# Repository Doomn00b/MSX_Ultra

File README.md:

# MSX_Ultra
 MSX2+ compatible Mini-ITX computer system, inspired by Sergey Kiselev's Omega Home Computer.

 This project is an open source implementation, and extension, of an MSX2+ compatible computer. The project is modular, and is built using a combination of 1980's-1990's era components - Z380 CPU, V9958 VDP, YM2610 PSG/FM-generator, and some newer components, such as 512 KiB SRAM and 512 KiB Flash ROM and dual FPGA's for the MSX-engine/Chipset (AT40K FPGAs).

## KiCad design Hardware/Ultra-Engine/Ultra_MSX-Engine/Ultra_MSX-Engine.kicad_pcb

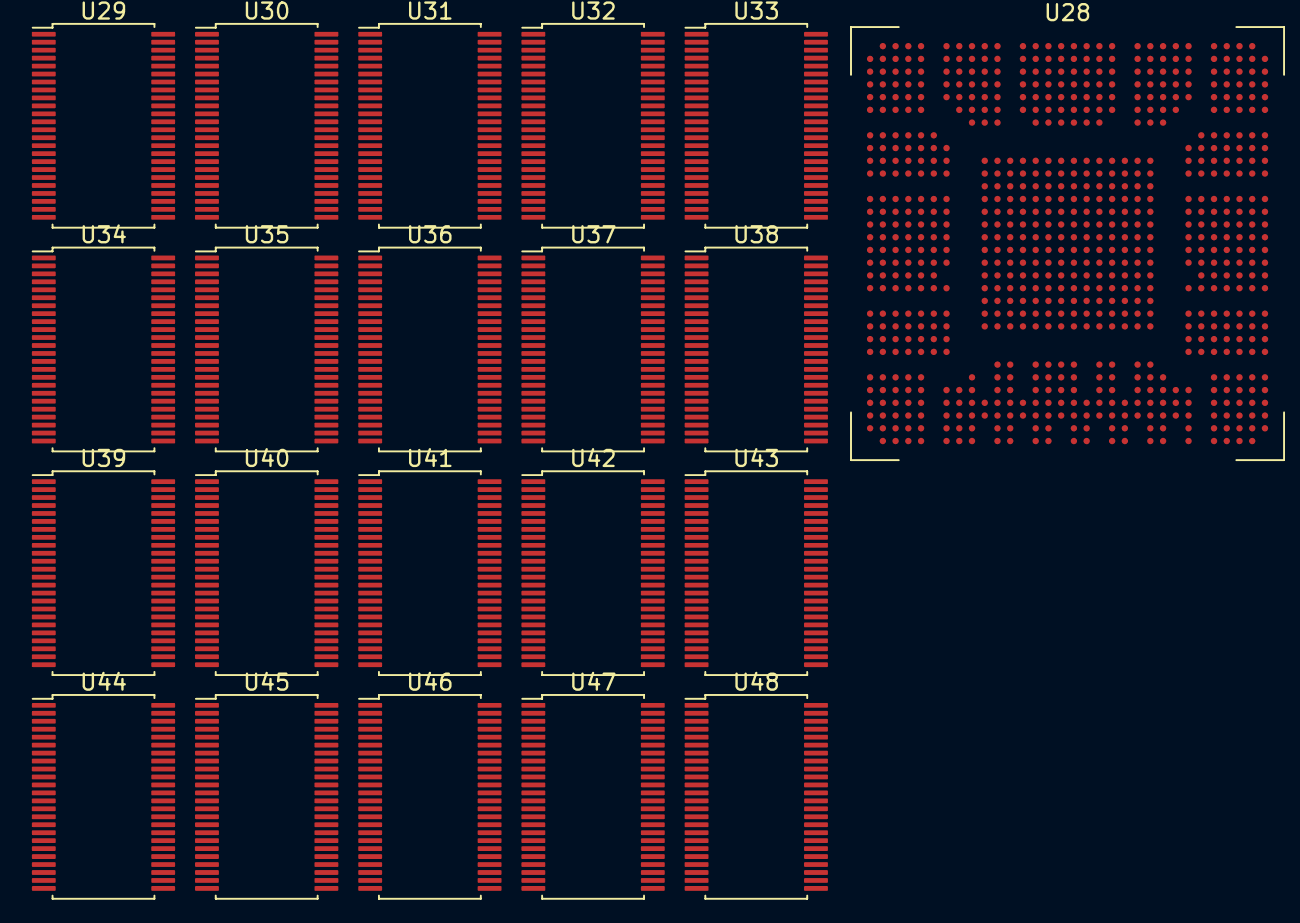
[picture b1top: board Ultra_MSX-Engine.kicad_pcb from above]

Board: 2 copper layers, 21 parts (0 on the bottom side), 35 nets, no tracks yet.

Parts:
U28: LFE5UM5G-85F-8BG756x; Lattice_caBGA-756_27.0x27.0mm_Layout27.8x27.8_P0.8mm
U29, U30, U31, U32, U33, U34, U35, U36, U37, U38, U39, U40, U41, U42, U43, U44, U45, U46, U47, U48: SN74LVCH16T245DGGR; TI_SN74LVCH16T245_6.2x12.6mm_P0.5mm

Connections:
unnamed: U28.AA11 (GND), U28.AA22 (GND), U28.AB11 (GND), U28.AB12 (GND), U28.AB13 (GND), U28.AB14 (GND), U28.AB15 (GND), U28.AB16 (GND), U28.AB17 (GND), U28.AB18 (GND), U28.AB19 (GND), U28.AB20 (GND), U28.AB21 (GND), U28.AB22 (GND), U28.AC12 (GND), U28.AC21 (GND), U28.AD2 (GND), U28.AD5 (GND), U28.AD28 (GND), U28.AD31 (GND), U28.AF11 (GND), U28.AF12 (GND), U28.AF14 (GND), U28.AF15 (GND), U28.AF16 (GND), U28.AF17 (GND), U28.AF19 (GND), U28.AF20 (GND), U28.AF23 (GND), U28.AG11 (GND), U28.AG14 (GND), U28.AG15 (GND), U28.AG16 (GND), U28.AG17 (GND), U28.AG20 (GND), U28.AG23 (GND), U28.AH2 (GND), U28.AH5 (GND), U28.AH7 (GND), U28.AH8 (GND), U28.AH11 (GND), U28.AH14 (GND), U28.AH15 (GND), U28.AH16 (GND), U28.AH17 (GND), U28.AH20 (GND), U28.AH23 (GND), U28.AH24 (GND), U28.AH25 (GND), U28.AH26 (GND), U28.AH29 (GND), U28.AH31 (GND), U28.AJ7 (GND), U28.AJ8 (GND), U28.AJ11 (GND), U28.AJ14 (GND), U28.AJ17 (GND), U28.AJ20 (GND), U28.AJ23 (GND), U28.AJ26 (GND), U28.AK7 (GND), U28.AK8 (GND), U28.AK11 (GND), U28.AK14 (GND), U28.AK17 (GND), U28.AK20 (GND), U28.AK23 (GND), U28.AK26 (GND), U28.AL2 (GND), U28.AL5 (GND), U28.AL7 (GND), U28.AL8 (GND), U28.AL9 (GND), U28.AL11 (GND), U28.AL12 (GND), U28.AL14 (GND), U28.AL15 (GND), U28.AL17 (GND), U28.AL18 (GND), U28.AL20 (GND), U28.AL21 (GND), U28.AL23 (GND), U28.AL24 (GND), U28.AL26 (GND), U28.AL29 (GND), U28.AL31 (GND), U28.AM7 (GND), U28.AM26 (GND), U28.B2 (GND), U28.B5 (GND), U28.B9 (GND), U28.B13 (GND), U28.B15 (GND), U28.B18 (GND), U28.B20 (GND), U28.B24 (GND), U28.B28 (GND), U28.B31 (GND), U28.E2 (GND), U28.E5 (GND), U28.E9 (GND), U28.E13 (GND), U28.E15 (GND), U28.E18 (GND), U28.E20 (GND), U28.E24 (GND), U28.E28 (GND), U28.E31 (GND), U28.J2 (GND), U28.J5 (GND), U28.J28 (GND), U28.J31 (GND), U28.K10 (GND), U28.K11 (GND), U28.K22 (GND), U28.K23 (GND), U28.L10 (GND), U28.L11 (GND), U28.L12 (GND), U28.L13 (GND), U28.L14 (GND), U28.L15 (GND), U28.L16 (GND), U28.L17 (GND), U28.L18 (GND), U28.L19 (GND), U28.L20 (GND), U28.L21 (GND), U28.L22 (GND), U28.L23 (GND), U28.M11 (GND), U28.M22 (GND), U28.N2 (GND), U28.N5 (GND), U28.N11 (GND), U28.N13 (GND), U28.N14 (GND), U28.N15 (GND), U28.N16 (GND), U28.N17 (GND), U28.N18 (GND), U28.N19 (GND), U28.N20 (GND), U28.N22 (GND), U28.N28 (GND), U28.N31 (GND), U28.P11 (GND), U28.P13 (GND), U28.P14 (GND), U28.P15 (GND), U28.P16 (GND), U28.P17 (GND), U28.P18 (GND), U28.P19 (GND), U28.P20 (GND), U28.P22 (GND), U28.R2 (GND), U28.R5 (GND), U28.R11 (GND), U28.R13 (GND), U28.R14 (GND), U28.R15 (GND), U28.R16 (GND), U28.R17 (GND), U28.R18 (GND), U28.R19 (GND), U28.R20 (GND), U28.R22 (GND), U28.R28 (GND), U28.R31 (GND), U28.T11 (GND), U28.T13 (GND), U28.T14 (GND), U28.T15 (GND), U28.T16 (GND), U28.T17 (GND), U28.T18 (GND), U28.T19 (GND), U28.T20 (GND), U28.T22 (GND), U28.U11 (GND), U28.U13 (GND), U28.U14 (GND), U28.U15 (GND), U28.U16 (GND), U28.U17 (GND), U28.U18 (GND), U28.U19 (GND), U28.U20 (GND), U28.U22 (GND), U28.V2 (GND), U28.V5 (GND), U28.V11 (GND), U28.V13 (GND), U28.V14 (GND), U28.V15 (GND), U28.V16 (GND), U28.V17 (GND), U28.V18 (GND), U28.V19 (GND), U28.V20 (GND), U28.V22 (GND), U28.V28 (GND), U28.V31 (GND), U28.W11 (GND), U28.W13 (GND), U28.W14 (GND), U28.W15 (GND)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
unnamed: U28.AA12 (VCC), U28.AA13 (VCC), U28.AA14 (VCC), U28.AA15 (VCC), U28.AA16 (VCC), U28.AA17 (VCC), U28.AA18 (VCC), U28.AA19 (VCC), U28.AA20 (VCC), U28.AA21 (VCC), U28.M12 (VCC), U28.M13 (VCC), U28.M14 (VCC), U28.M15 (VCC), U28.M16 (VCC), U28.M17 (VCC), U28.M18 (VCC), U28.M19 (VCC), U28.M20 (VCC), U28.M21 (VCC), U28.N12 (VCC), U28.N21 (VCC), U28.P12 (VCC), U28.P21 (VCC), U28.R12 (VCC), U28.R21 (VCC), U28.T12 (VCC), U28.T21 (VCC), U28.U12 (VCC), U28.U21 (VCC), U28.V12 (VCC), U28.V21 (VCC), U28.W12 (VCC), U28.W21 (VCC), U28.Y12 (VCC), U28.Y21 (VCC)
unnamed: U28.AG9 (VCCA0), U28.AG12 (VCCA0), U28.AH9 (VCCA0), U28.AH12 (VCCA0), U28.AJ9 (VCCA0), U28.AJ10 (VCCA0), U28.AJ12 (VCCA0), U28.AJ13 (VCCA0)
unnamed: U28.AF22 (VCCA1), U28.AG19 (VCCA1), U28.AG22 (VCCA1), U28.AH19 (VCCA1), U28.AH22 (VCCA1), U28.AJ18 (VCCA1), U28.AJ19 (VCCA1), U28.AJ21 (VCCA1), U28.AJ22 (VCCA1)
unnamed: U28.AC11 (VCCAUX), U28.AC22 (VCCAUX), U28.K13 (VCCAUX), U28.K20 (VCCAUX), U28.N10 (VCCAUX), U28.N23 (VCCAUX), U28.Y10 (VCCAUX), U28.Y23 (VCCAUX)
unnamed: U28.AJ15 (VCCAUXA0), U28.AJ16 (VCCAUXA0)
unnamed: U28.AJ24 (VCCAUXA1), U28.AJ25 (VCCAUXA1)
unnamed: U28.K12 (VCCIO0), U28.K14 (VCCIO0), U28.K15 (VCCIO0), U28.K16 (VCCIO0)
unnamed: U28.K17 (VCCIO1), U28.K18 (VCCIO1), U28.K19 (VCCIO1), U28.K21 (VCCIO1)
unnamed: U28.M23 (VCCIO2), U28.P23 (VCCIO2), U28.R23 (VCCIO2), U28.T23 (VCCIO2)
unnamed: U28.AA23 (VCCIO3), U28.U23 (VCCIO3), U28.V23 (VCCIO3), U28.W23 (VCCIO3)
unnamed: U28.AB23 (VCCIO4), U28.AC23 (VCCIO4)
unnamed: U28.AA10 (VCCIO6), U28.U10 (VCCIO6), U28.V10 (VCCIO6), U28.W10 (VCCIO6)
unnamed: U28.M10 (VCCIO7), U28.P10 (VCCIO7), U28.R10 (VCCIO7), U28.T10 (VCCIO7)
unnamed: U28.AB10 (VCCIO8), U28.AC10 (VCCIO8)
unnamed: U29.4 (GND), U29.10 (GND_2), U29.15 (GND_3), U29.21 (GND_4), U29.28 (GND_5), U29.34 (GND_6), U29.39 (GND_7), U29.45 (GND_8)
unnamed: U30.4 (GND), U30.10 (GND_2), U30.15 (GND_3), U30.21 (GND_4), U30.28 (GND_5), U30.34 (GND_6), U30.39 (GND_7), U30.45 (GND_8)
unnamed: U31.4 (GND), U31.10 (GND_2), U31.15 (GND_3), U31.21 (GND_4), U31.28 (GND_5), U31.34 (GND_6), U31.39 (GND_7), U31.45 (GND_8)
unnamed: U32.4 (GND), U32.10 (GND_2), U32.15 (GND_3), U32.21 (GND_4), U32.28 (GND_5), U32.34 (GND_6), U32.39 (GND_7), U32.45 (GND_8)
unnamed: U33.4 (GND), U33.10 (GND_2), U33.15 (GND_3), U33.21 (GND_4), U33.28 (GND_5), U33.34 (GND_6), U33.39 (GND_7), U33.45 (GND_8)
unnamed: U34.4 (GND), U34.10 (GND_2), U34.15 (GND_3), U34.21 (GND_4), U34.28 (GND_5), U34.34 (GND_6), U34.39 (GND_7), U34.45 (GND_8)
unnamed: U35.4 (GND), U35.10 (GND_2), U35.15 (GND_3), U35.21 (GND_4), U35.28 (GND_5), U35.34 (GND_6), U35.39 (GND_7), U35.45 (GND_8)
unnamed: U36.4 (GND), U36.10 (GND_2), U36.15 (GND_3), U36.21 (GND_4), U36.28 (GND_5), U36.34 (GND_6), U36.39 (GND_7), U36.45 (GND_8)
unnamed: U37.4 (GND), U37.10 (GND_2), U37.15 (GND_3), U37.21 (GND_4), U37.28 (GND_5), U37.34 (GND_6), U37.39 (GND_7), U37.45 (GND_8)
unnamed: U38.4 (GND), U38.10 (GND_2), U38.15 (GND_3), U38.21 (GND_4), U38.28 (GND_5), U38.34 (GND_6), U38.39 (GND_7), U38.45 (GND_8)
unnamed: U39.4 (GND), U39.10 (GND_2), U39.15 (GND_3), U39.21 (GND_4), U39.28 (GND_5), U39.34 (GND_6), U39.39 (GND_7), U39.45 (GND_8)
unnamed: U40.4 (GND), U40.10 (GND_2), U40.15 (GND_3), U40.21 (GND_4), U40.28 (GND_5), U40.34 (GND_6), U40.39 (GND_7), U40.45 (GND_8)
unnamed: U41.4 (GND), U41.10 (GND_2), U41.15 (GND_3), U41.21 (GND_4), U41.28 (GND_5), U41.34 (GND_6), U41.39 (GND_7), U41.45 (GND_8)
unnamed: U42.4 (GND), U42.10 (GND_2), U42.15 (GND_3), U42.21 (GND_4), U42.28 (GND_5), U42.34 (GND_6), U42.39 (GND_7), U42.45 (GND_8)
unnamed: U43.4 (GND), U43.10 (GND_2), U43.15 (GND_3), U43.21 (GND_4), U43.28 (GND_5), U43.34 (GND_6), U43.39 (GND_7), U43.45 (GND_8)
unnamed: U44.4 (GND), U44.10 (GND_2), U44.15 (GND_3), U44.21 (GND_4), U44.28 (GND_5), U44.34 (GND_6), U44.39 (GND_7), U44.45 (GND_8)
unnamed: U45.4 (GND), U45.10 (GND_2), U45.15 (GND_3), U45.21 (GND_4), U45.28 (GND_5), U45.34 (GND_6), U45.39 (GND_7), U45.45 (GND_8)
unnamed: U46.4 (GND), U46.10 (GND_2), U46.15 (GND_3), U46.21 (GND_4), U46.28 (GND_5), U46.34 (GND_6), U46.39 (GND_7), U46.45 (GND_8)
unnamed: U47.4 (GND), U47.10 (GND_2), U47.15 (GND_3), U47.21 (GND_4), U47.28 (GND_5), U47.34 (GND_6), U47.39 (GND_7), U47.45 (GND_8)
unnamed: U48.4 (GND), U48.10 (GND_2), U48.15 (GND_3), U48.21 (GND_4), U48.28 (GND_5), U48.34 (GND_6), U48.39 (GND_7), U48.45 (GND_8)

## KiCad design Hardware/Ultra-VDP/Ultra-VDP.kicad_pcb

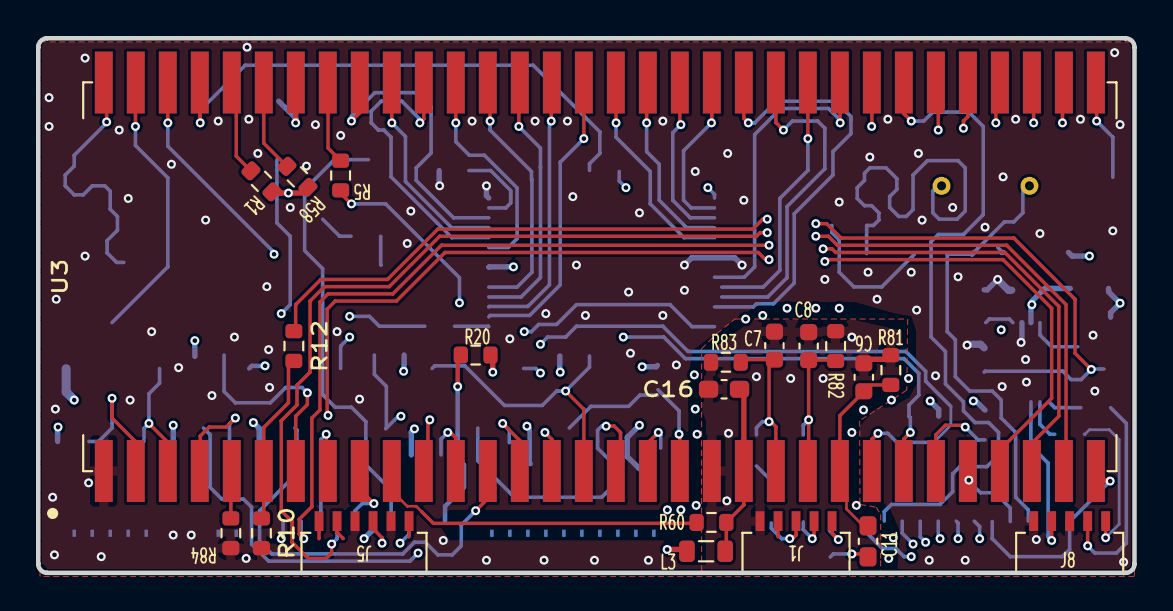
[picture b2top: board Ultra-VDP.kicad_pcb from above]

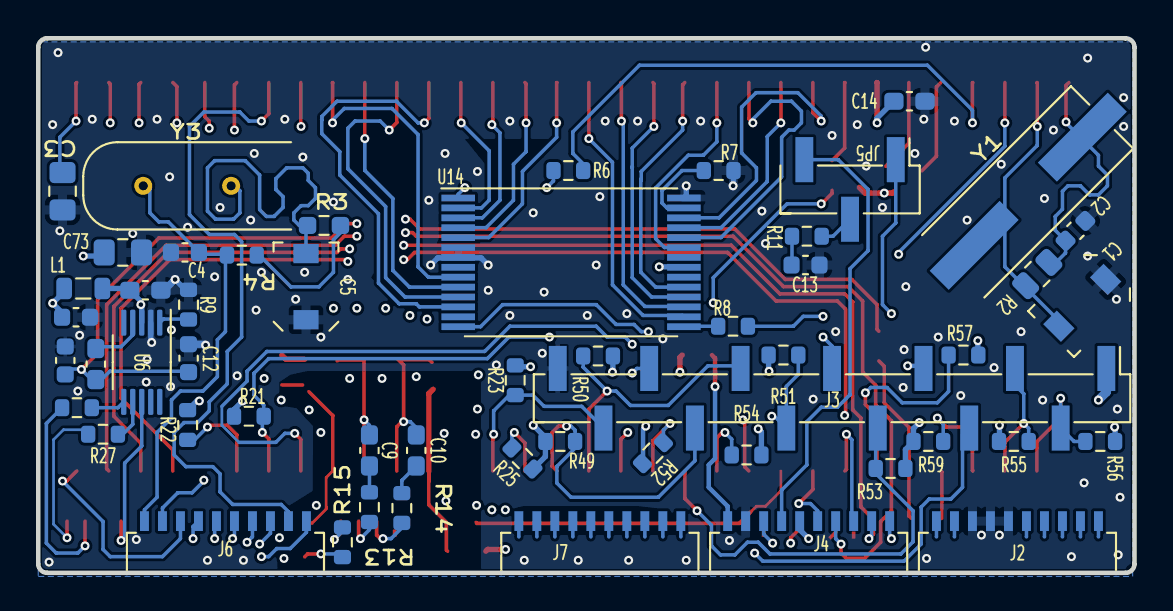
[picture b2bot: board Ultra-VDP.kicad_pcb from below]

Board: 4 copper layers, 60.9 x 29.7 mm, 95 parts (70 on the bottom side), 110 nets.

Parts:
C1, C5: CTRIM_SGC3S300NM; C_Trimmer_Sprague-Goodman_SGC3
C2, C4: 22pF; C_0603_1608Metric
C3: C_CL21B223KBANFNC; C_0805_2012Metric_Pad1.18x1.45mm_HandSolder
C6, C7, C8: 330pF; C_0603_1608Metric
C9, C10, C11, C14, C15, C16, C17: C_CL10B104KB8NNNL; C_0603_1608Metric_Pad1.08x0.95mm_HandSolder
C12, C19: C_CC0603JRNPO9BN470; C_0603_1608Metric
C13: 4.7pF; C_0603_1608Metric
C18: C_GRM188D71A106KA73D; C_0603_1608Metric
C73: C_GRM21BR71A106KA73K; C_0805_2012Metric_Pad1.18x1.45mm_HandSolder
J1, J8: BC075-05; GCT_BC075-05_PinHeader_1x05_P1.00mm_Horizontal_SMD
J2, J4, J6, J7: BC075-10; GCT_BC075-10_PinHeader_1x10_P1.00mm_Horizontal_SMD
J3: CBUS; PinHeader_1x13_P2.54mm_Vertical_SMD_Pin1Left_lrj
J5: BC075-06; GCT_BC075-06_PinHeader_1x06_P1.00mm_Horizontal_SMD
JP5: NTSC/PAL; PinHeader_1x03_P2.54mm_Vertical_SMD_Pin1Left_sc
L1, L3: L_MLZ2012M4R7HT000; L_0805_2012Metric
R1, R7, R9, R20, R21, R22, R23, R25, R49, R50, R51, R52, R53, R54, R55, R56, R57, R58, R59, R60: R_RC0603FR-0710KL; R_0603_1608Metric_roundcourt
R2: 470k; R_0805_2012Metric
R3: R_ERA-3VRW1001V; R_0603_1608Metric_Pad0.98x0.95mm_HandSolder
R4: R_ERJ-3GEYJ105V; R_0603_1608Metric
R5, R6, R8, R12, R27, R61: R_CRGP0603F220R; R_0603_1608Metric
R10, R13, R14, R15: R_ERJ-PA3F75R0V; R_0603_1608Metric_roundcourt
R11: 2.2k; R_0603_1608Metric
R81, R82, R83, R84: R_CRG0603F470R; R_0603_1608Metric
U3: V9958; DIP-64_W19.05mm_SMDSocket_SmallPads
U6: LMH1980; VSSOP-10_3x3mm_P0.5mm
U14: V53C8125HT30; TSOP-I-28_11.8x8mm_P0.55mm
Y1: Y_HCM4921477270ABJT; Crystal_HC49-US_Vertical_SMD
Y3: Y_ECS-44-20-4X; Crystal_HC49-US_Vertical_THT
trace1, trace2, trace3, trace4, trace6, trace7, trace8, trace9, trace10, trace11, trace12, trace13, trace14, trace15, trace16, trace17, trace18, trace19, trace20, trace21, trace22: pcb-trace; NetTie-2_SMD_Pad0.2mm

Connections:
+5V: C14.2, C18.1, C73.1, J3.1, J4.5, L1.1, L3.1, R1.1, R20.1, R21.2, R22.2, R23.2, R25.2, R49.2, R50.2, R51.2, R52.2, R53.2, R54.2, R55.2, R56.2, R57.2, R58.2, R59.2, U3.58 (VDD), U14.21 (VCC)
/A0: J5.4, U3.29 (MODE0)
/A1: J6.2, U3.28 (MODE1)
/A2: J7.4, trace9.1
/A3: J7.5, trace10.1
/A4: J7.6, trace11.1
/A5: J7.7, trace12.1
/A6: J7.8, trace13.1
/A7: J7.9, trace14.1
/A8: J7.10, trace15.1
/B-Mb: J1.5, R15.2
/BLANK: J5.6, trace4.1
/BLEO: R57.1, U3.7 (BLEO)
/BLUE1: C6.1, C11.2, R81.1, U3.24 (B)
/BLUE2: C11.1, R15.1
/CB0: J3.12, R23.1, U3.19 (C0)
/CB1: J3.11, R25.1, U3.18 (C1)
/CB2: J3.10, R49.1, U3.17 (C2)
/CB3: J3.9, R50.1, U3.16 (C3)
/CB4: J3.8, R51.1, U3.15 (C4)
/CB5: J3.7, R52.1, U3.14 (C5)
/CB6: J3.6, R53.1, U3.13 (C6)
/CB7: J3.5, R54.1, U3.12 (C7)
/CBDR: J3.4, U3.11 (CBDR)
/CLK_VDP: J4.8, U3.8 (~VDS/CPUCLK)
/COMPSYNC: R10.2, R12.2, U3.6 (CSYNC)
/CSYNC: J8.2, U6.8 (CSOUT)
/D0: J6.10, U3.40 (CD0)
/D1: J6.9, U3.39 (CD1)
/D2: J6.8, U3.38 (CD2)
/D3: J6.7, U3.37 (CD3)
/D4: J6.6, U3.36 (CD4)
/D5: J6.5, U3.35 (CD5)
/D6: J6.4, U3.34 (CD6)
/D7: J6.3, U3.32 (CD7)
/D8: J2.2, trace17.1
/D9: J2.1, trace16.1
/D10: J5.1, trace2.1
/D11: J5.2, trace3.1
/D12: J2.6, trace18.1
/D13: J7.1, trace6.1
/D14: J7.2, trace7.1
/D15: J7.3, trace8.1
/G-Mb: J1.3, R14.2
/GREEN1: C7.1, C10.2, R83.1, U3.22 (G)
/GREEN2: C10.1, R14.1
/HORSYNC: R84.1, U3.5 (HSYNC)
/HSYNC: J8.4, R61.1
/NTSC_CLKO: J4.10, JP5.1
/PAL_CLK_IN+: C4.2, J6.1, R4.1, Y3.1
/PAL_CLK_IN-: C5.2, R3.2, Y3.2
/PAL_CLK_OUT: J4.4, JP5.3
/R-Mb: J1.4, R13.2
/RED1: C8.1, C9.2, R82.1, U3.23 (R)
/RED2: C9.1, R13.1
/SYNCIN: C15.1, U6.4 (VIN)
/TCK: J2.9, trace21.1
/TDI: J2.8, trace20.1
/TDO: J2.10, trace22.1
/TMS: J2.7, trace19.1
/VA0: U3.49 (AD0), U14.16 (A0)
/VA1: U3.50 (AD1), U14.17 (A1)
/VA2: U3.51 (AD2), U14.18 (A2)
/VA3: U3.52 (AD3), U14.19 (A3)
/VA4: U3.53 (AD4), U14.23 (A4)
/VA5: U3.54 (AD5), U14.24 (A5)
/VA6: U3.55 (AD6), U14.25 (A6)
/VA7: U3.56 (AD7), U14.26 (A7)
/VD0: U3.41 (RD0), U14.9 (IO1)
/VD1: U3.42 (RD1), U14.10 (IO2)
/VD2: U3.43 (RD2), U14.11 (IO3)
/VD3: U3.44 (RD3), U14.12 (IO4)
/VD4: U3.45 (RD4), U14.2 (IO5)
/VD5: U3.46 (RD5), U14.3 (IO6)
/VD6: U3.47 (RD6), U14.4 (IO7)
/VD7: U3.48 (RD7), U14.5 (IO8)
/VREF: J1.2, trace1.1
/VSYNC: J8.5, R27.1
/V_CLK: C13.1, R11.1
/XTAL1+: C1.2, R2.2, U3.63 (XTAL1/CLKIN), Y1.2
/XTAL-: C2.2, R2.1, U3.64 (XTAL2), Y1.1
/~CAS0: R6.1, U14.1 (~CAS)
/~CAS1: R1.2, U3.60 (~CAS1)
/~CASX: R58.1, U3.59 (~CASX)
/~DHCLK: J3.2, R56.1, U3.2 (~DHCLK)
/~DLCLK: J3.3, R55.1, U3.3 (~DLCKL)
/~HRESET: R22.1, U3.27 (~HRESET)
/~RAS_: R8.2, U3.62 (~RAS)
/~RAS: R8.1, U14.15 (~RAS)
/~RESET: J4.6, U3.9 (~RESET)
/~VDP_INT: J4.1, R20.2, U3.25 (~INT)
/~VDP_RD: J4.7, U3.31 (~CSR)
/~VDP_WAIT: J4.3, R21.1, U3.26 (~WAIT)
/~VDP_WR: J4.9, U3.30 (~CSW)
/~VRESET: R59.1, U3.4 (~VRESET)
/~VWR: R5.1, U14.14 (~WE)
/~YS: R60.1, U3.10 (~YS)
GND: C1.1, C2.1, C3.2, C4.1, C5.1, C6.2, C7.2, C8.2, C12.2, C13.2, C14.1, C16.1, C17.2, C18.2, C19.2, C73.2, J1.1, J2.3, J2.4, J2.5, J3.13, J4.2, J5.3, J5.5, J8.1, J8.3, R7.1, R9.1, R10.1, R81.2, R82.2, R83.2, R84.2, U3.1 (GND), U3.20 (GNDA), U6.2 (GND), U14.6 (VSS), U14.7 (VSS), U14.28 (~OE)
unnamed: C12.1, C15.2, C19.1, R12.1
unnamed: JP5.2, R11.2
unnamed: R3.1, R4.2
unnamed: R5.2, U3.57 (R/~W)
unnamed: R6.2, U3.61 (~CAS0)
unnamed: C3.1, U3.33 (VBB)
unnamed: R61.2, U6.6 (HSOUT)
unnamed: R9.2, U6.1 (REXT)
unnamed: R27.2, U6.7 (VSOUT)
unnamed: R7.2, U14.27 (A8)
VCCVDP: C16.2, L3.2, R60.2, U3.21 (VDDA)
VDDSYNC: C17.1, L1.2, U6.3 (VCC)

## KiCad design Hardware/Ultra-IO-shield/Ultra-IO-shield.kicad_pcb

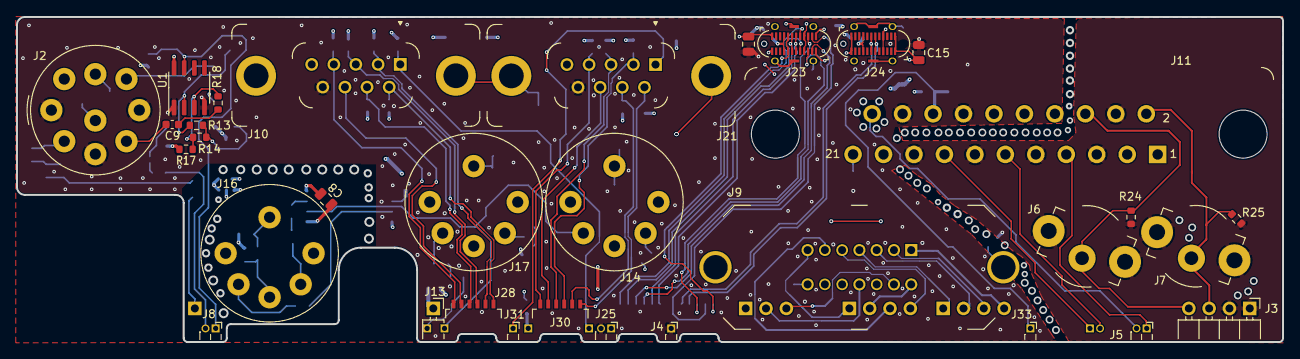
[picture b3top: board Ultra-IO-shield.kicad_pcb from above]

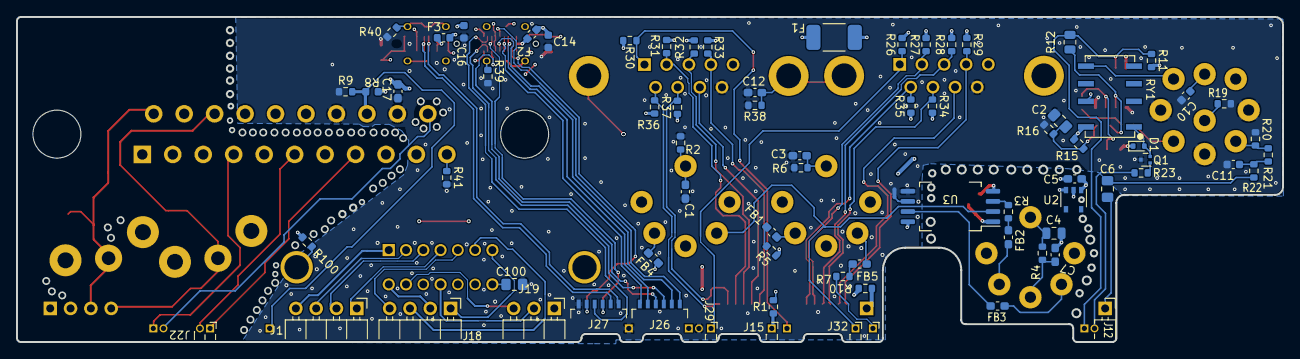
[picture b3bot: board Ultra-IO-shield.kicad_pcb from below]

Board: 4 copper layers, 158.3 x 40.6 mm, 108 parts (75 on the bottom side), 93 nets.

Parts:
C1, C3, C5, C7, C12, C17: C_CL10B104KB8NNNL; C_0603_1608Metric_Pad1.08x0.95mm_HandSolder
C2: C_GRM21BR71A106KA73K; C_0805_2012Metric_Pad1.18x1.45mm_HandSolder
C4, C8: C_CL21B103KBANNNC; C_0805_2012Metric
C6, C100: C_CL21B105KBFNNNF; C_0805_2012Metric_Pad1.18x1.45mm_HandSolder
C9, C11: 22nF; C_0603_1608Metric
C10: 0.1uF; C_0603_1608Metric
C13, C15: C_GRM21BR61A476ME15K; C_0805_2012Metric
C14, C16: C_CL10B104KB8NNNL; C_0603_1608Metric_round_court
D1: 1N4148WT; D_SOD-523
F1: PPTC_SMD1812B075TF; Yageo_Fuse_1812_4532Metric
F2, F3: PPTC_0603L075; Fuse_0603_1608Metric
FB1, FB2, FB3, FB4, FB5: L_ferrite_BLM18KG102SZ1D; L_0603_1608Metric_Pad1.05x0.95mm_HandSolder
J1, J3, J18: Conn_01x04; PinHeader_1x04_P2.54mm_Horizontal_less-silk
J2: DIN-8_SD-80BV; Jack_DIN_CUI_SD-80BV_Vertical
J4, J15, J20, J29, J31, J32, J33: Conn_01x02; PinHeader_1x01_P1.27mm_Horizontal_less-silk
J5, J8, J22, J25: Conn_01x02; PinHeader_1x02_P1.27mm_Horizontal_less-silk
J6: Conn_RCJ-023; CUI_RCJ-023
J7: Conn_RCJ-022; CUI_RCJ-022
J9: NorComp_111-014-213L001; Conn_Micro_Ribbon_14F_Vertical
J10, J21: ASSMANN_A-DF_09_PP/Z; Assmann_A-DF09PP_Z_Female_Vertical_P2.77x2.84mm
J11: TC_1578891_SCART; SCART-21_Female_Vertical_P1.905x2.54mm_EdgePinOffset10.7mm
J12, J13: Conn_01x01; PinHeader_1x01_P2.54mm_Horizontal_less-silk
J14, J16, J17: CUI_SD-50BV; Jack_DIN_CUI_SD-50BV_Vertical
J19: Conn_01x03; PinHeader_1x03_P2.54mm_Horizontal_less-silk
J23, J24: USB_C_GCT_USB4115-03-C; GCT_USB4115-03-C_modified
J26, J27, J28, J30: BC075-06; GCT_BC075-06_PinHeader_1x06_P1.00mm_Horizontal_SMD_less-silk
Q1: MMBT2907AM3T5G; SOT-723
R1, R3, R5, R7: R_CRGP0603F220R; R_0603_1608Metric
R2, R4, R6, R19, R38, R39, R40, R41, R100: R_ERJ-3GEYJ105V; R_0603_1608Metric
R8: 100; C_0603_1608Metric_round_court
R9: 100; R_0603_1608Metric
R10: 1k; R_0603_1608Metric
R11, R23: 1K; R_0603_1608Metric
R12: 220K; R_0805_2012Metric_roundcourt
R13, R21, R22: 4.7K; R_0603_1608Metric
R14, R18: 10K; R_0603_1608Metric
R15, R16: 2.7K; R_0603_1608Metric
R17: 470K; R_0603_1608Metric
R20: 100R; R_0603_1608Metric
R24, R25: 47k; R_0603_1608Metric
R26, R27, R28, R29, R30, R31, R32, R33, R34, R35, R36, R37: R_RC0603FR-074K7L; R_0603_1608Metric
RY1: TE_IM43GR; Relay_DPDT_AXICOM_IMSeries_GullWing
TP1: NetTie-2_small_round; NetTie-2_SMD_Pad0.5mm
U1: LM211; SOIC-8_3.9x4.9mm_P1.27mm
U2: AP7370; DIODES_SOT-753_SC-74A
U3: ADuM226; TEXAS_RI-8-1_7.5x5.85mm_P1.27mm

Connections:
+5V: C14.1, C16.1, D1.1 (K), F1.1, F2.2, F3.2, J15.1, J19.1, J25.1, R1.1, R5.1, R8.1, R11.2, R15.2, R17.1, R26.2, R27.2, R28.2, R29.2, R30.2, R31.2, R32.2, R33.2, R34.2, R35.2, R36.2, R37.2, RY1.8, U1.8 (V+), U3.8 (VDD2)
+12V: C5.1, J13.1, R10.2, U2.1 (VIN)
/+5VD: C8.1, U2.3 (VOUT), U3.1 (VDD1)
/+5_joy: F1.2, J10.5, J21.5
/+12V-1K: C17.1, J11.8 (SW), R10.1
/AUD_L: J3.4, J6.2 (IN2), J11.6 (AIL/MONO), R24.1
/AUD_R: J3.3, J7.2 (IN2), J11.2 (AIR), R25.2
/BLANK: J11.16 (BLNK), J33.1, R8.2, R9.1
/BOUT: J5.1, J11.7 (BLUE)
/CAS_I: C9.1, J2.5
/CAS_IN: J8.1, R11.1, R12.2, U1.7 (COL_OUT)
/CAS_MOT: J8.2, R23.1
/CAS_O: J2.4, R20.1, R21.2
/CAS_OUT: C6.2, J12.1
/CC1/HPD: J23.A5 (CC1), J23.B5 (CC2), J27.2
/CSINKi: FB3.1, U3.7 (VIA)
/CSINKo: FB1.2, R5.2
/CSRCi: R3.1, U3.3 (VIB)
/CSRCo: FB5.1, R7.2
/CSYNC: J5.2, J11.20 (VIDIN/Sync)
/GND_U: C13.1, C15.1, J23.A1 (GND), J23.A12 (GND), J23.B1 (GND), J23.B12 (GND), J24.A1 (GND), J24.A12 (GND), J24.B1 (GND), J24.B12 (GND)
/GND/SBU2: J23.B8 (SBU2), J26.5
/GOUT: J11.11 (GREEN), J22.2
/JOY_OUT_A: J10.8, J28.2
/JOY_OUT_B: J21.8, J30.2
/MID_RX: J14.5, J32.1, U3.2 (VOA)
/MID_TX: J20.1, R7.1
/N_O: J2.7, RY1.5
/PD0: J1.3, J9.2
/PD1: J1.2, J9.3
/PD2: J1.1, J9.4
/PD3: J9.5, J18.4
/PD4: J9.6, J18.3
/PD5: J9.7, J18.1
/PD6: J9.8, J18.2
/PD7: J9.9, J19.3
/PRT_BUSY: J9.11, J19.2
/ROUT: J11.15 (RED/CHROMA), J22.1
/RY_5V: J2.6, RY1.7
/SH1: J23.SH (SHIELD), R39.2
/SH2: J24.SH (SHIELD), R40.2
/SH3: J11.21 (SH), R41.1
/SWDCLK/RX1-: J23.B10 (RX1-), J26.3
/SWDIO/RX1+: J23.B11 (RX1+), J26.4
/SWO/RX2-: J23.A10 (RX2-), J27.4
/USB1_D+: J23.A7 (D1-), J23.B7 (D2-), J26.1
/USB1_D-: J23.A6 (D1+), J23.B6 (D2+), J26.2
/USB2_D+: J24.A6 (D1+), J24.B6 (D2+), J27.6
/USB2_D-: J24.A7 (D1-), J24.B7 (D2-), J27.5
/VBUS1: F2.1, J23.A4 (VBUS), J23.A9 (VBUS), J23.B4 (VBUS), J23.B9 (VBUS)
/VBUS2: F3.1, J24.A4 (VBUS), J24.A9 (VBUS), J24.B4 (VBUS), J24.B9 (VBUS)
/VCT/SBU1: J23.A8 (SBU1), J26.6
/nRESET/RX2+: J23.A11 (RX2+), J27.3
/~BCK_A: J10.2, J28.5, R27.1
/~BCK_B: J21.2, J30.4, R31.1
/~FWD_A: J10.1, J29.1, R26.1
/~FWD_B: J21.1, J31.1, R30.1
/~LFT_A: J10.3, J28.4, R28.1
/~LFT_B: J21.3, J30.3, R32.1
/~RGT_A: J10.4, J28.1, R29.1
/~RGT_B: J21.4, J30.1, R33.1
/~STROBE: J1.4, J9.1
/~TRG1_A: J10.6, J28.6, R35.1
/~TRG1_B: J21.6, J30.6, R36.1
/~TRG2_A: J10.7, J28.3, R34.1
/~TRG2_B: J21.7, J30.5, R37.1
GND: C1.2, C2.2, C3.2, C10.2, C11.2, C12.2, C13.2, C14.2, C15.2, C16.2, C17.2, C100.2, J2.1, J2.2, J2.3, J3.1, J3.2, J4.1, J6.1A (IN1), J6.1B (IN1), J7.1A (IN1), J7.1B (IN1), J10.9, J11.4 (AUGND), J11.5 (BGND), J11.9 (GGND), J11.13 (RGND), J11.14 (DATGND), J11.17 (VGND), J11.18 (BLNKGND), J21.9, J25.2, J27.1, Q1.3 (C), R2.1, R6.1, R9.2, R16.2, R19.1, R20.2, R24.2, R25.1, R38.1, R39.1, R40.1, R41.2, R100.1, TP1.1, U1.1 (GND), U1.4 (V-), U3.5 (GND2)
GND2: C4.2, C5.2, C7.2, C8.2, U2.2 (GND), U3.4 (GND1)
unnamed: C1.1, J14.2, J14.G, R2.2
unnamed: C2.1, R13.1, R14.2, R15.1, R16.1
unnamed: C3.1, J17.2, J17.G, R6.2
unnamed: C4.1, J16.G, R4.2
unnamed: C6.1, R22.1
unnamed: C7.1, J16.2, R4.1
unnamed: C9.2, R18.2
unnamed: C10.1, J2.SH
unnamed: C11.1, R21.1, R22.2
unnamed: C12.1, J10.SH, J21.SH, R38.2
unnamed: D1.2 (A), Q1.2 (E), RY1.1
unnamed: FB1.1, J17.4
unnamed: FB2.1, J16.4
unnamed: FB2.2, R3.2
unnamed: FB3.2, J16.5
unnamed: FB4.1, J14.4
unnamed: FB4.2, R1.2
unnamed: FB5.2, J17.5
unnamed: J2.8, R19.2
unnamed: C100.1, J9.14
unnamed: J9.15 (SH), J9.16 (SH2), R100.2
unnamed: Q1.1 (B), R23.2
unnamed: R12.1, R13.2, U1.2 (+)
unnamed: R14.1, R17.2, R18.1, U1.3 (-)
unnamed: TP1.2, U3.6 (VOB)

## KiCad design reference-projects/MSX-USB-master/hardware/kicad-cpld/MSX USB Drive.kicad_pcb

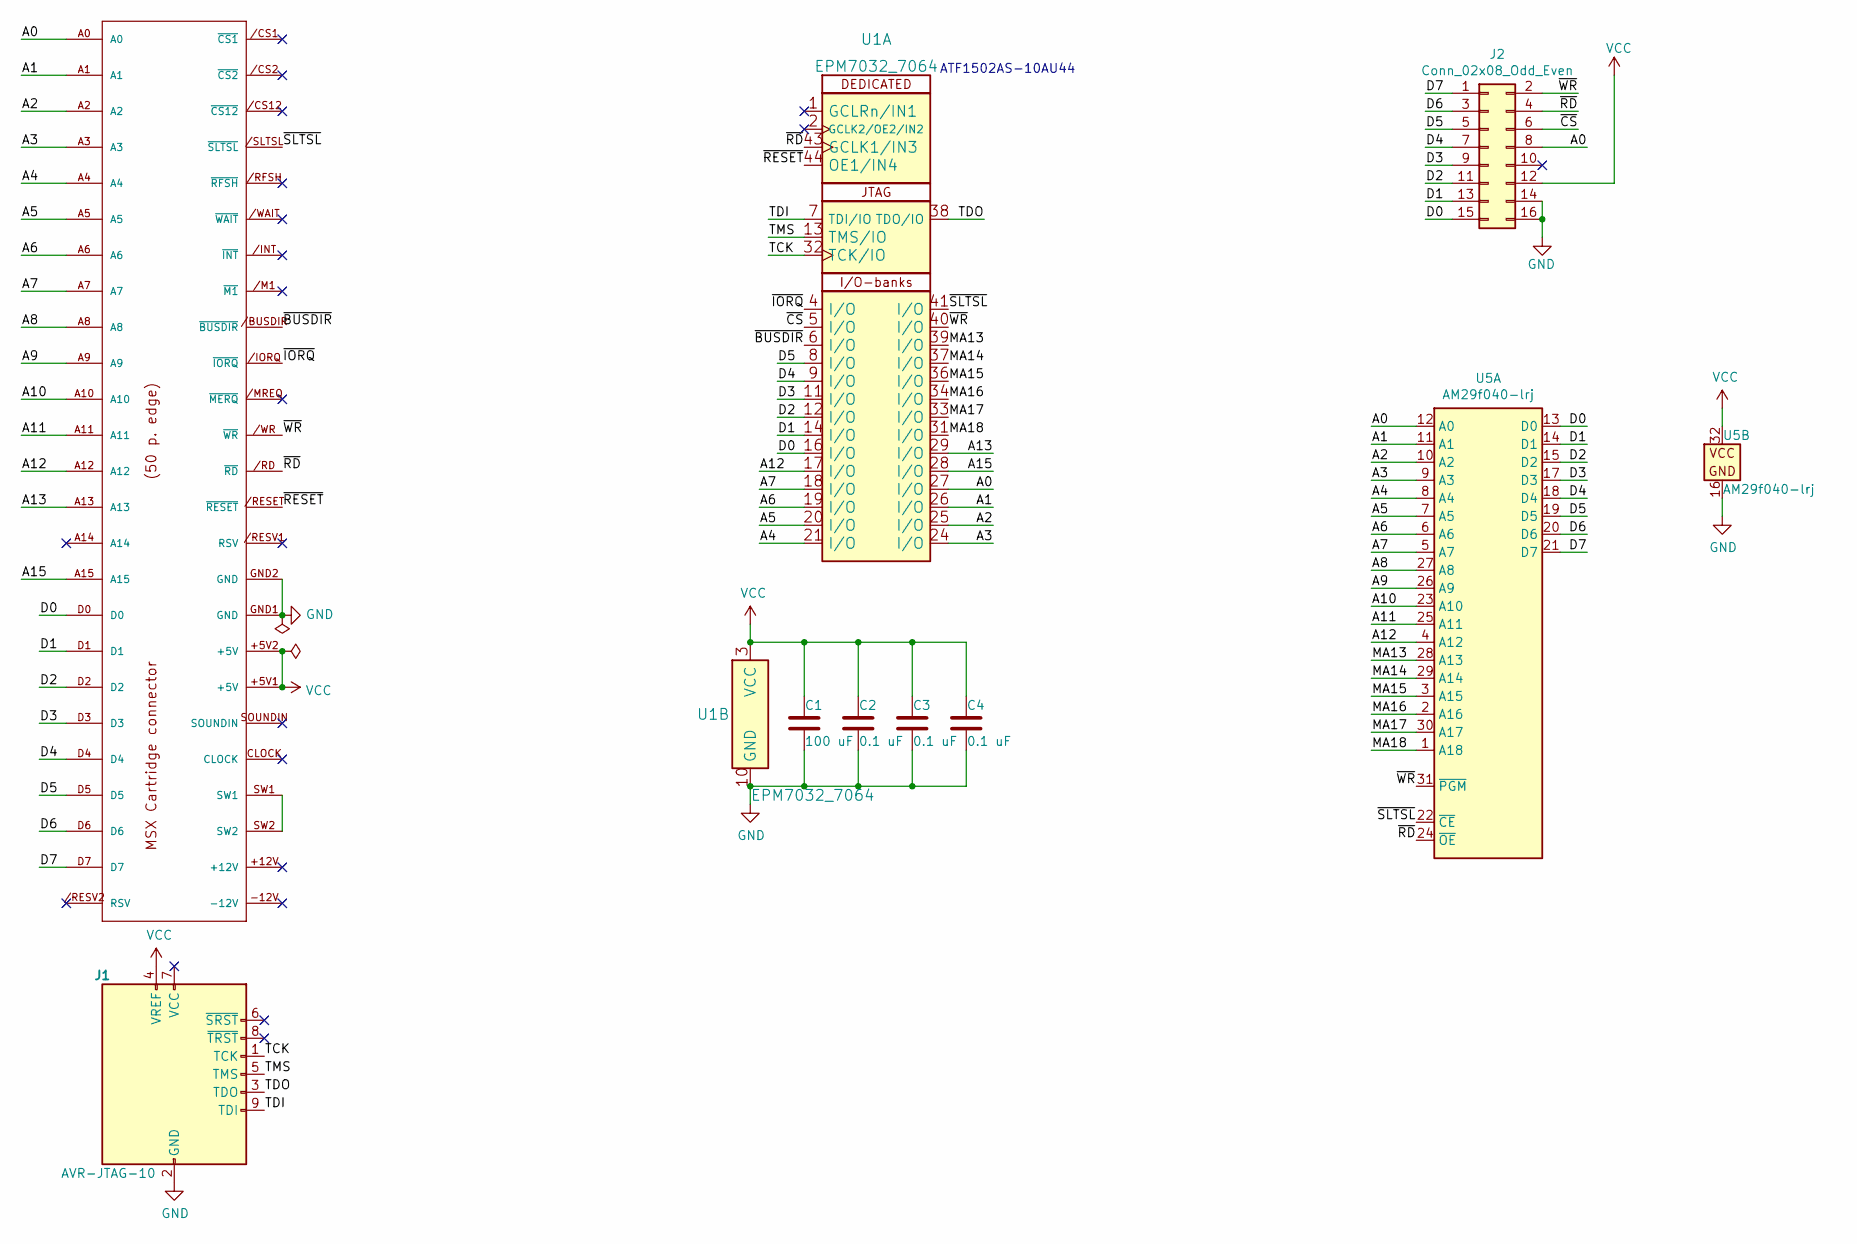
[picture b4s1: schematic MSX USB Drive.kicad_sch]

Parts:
C1: 100 uF; CP_Elec_6.3x5.4
C2, C3, C4: 0.1 uF; C_0805_2012Metric_Pad1.15x1.40mm_HandSolder
EDG1: MSX_CON; msx-con-MSXCART
J1: AVR-JTAG-10; PinHeader_2x05_P2.54mm_Vertical
J2: Conn_02x08_Odd_Even; PinHeader_2x08_P2.54mm_Vertical
U1: EPM7032_7064; PLCC44
U5: AM29f040-lrj; DIP-32_W15.24mm_Socket; MPN AM29f040

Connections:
/A0: EDG1.A0, J2.8, U1.27 (I/O), U5.12 (A0)
/A1: EDG1.A1, U1.26 (I/O), U5.11 (A1)
/A2: EDG1.A2, U1.25 (I/O), U5.10 (A2)
/A3: EDG1.A3, U1.24 (I/O), U5.9 (A3)
/A4: EDG1.A4, U1.21 (I/O), U5.8 (A4)
/A5: EDG1.A5, U1.20 (I/O), U5.7 (A5)
/A6: EDG1.A6, U1.19 (I/O), U5.6 (A6)
/A7: EDG1.A7, U1.18 (I/O), U5.5 (A7)
/A8: EDG1.A8, U5.27 (A8)
/A9: EDG1.A9, U5.26 (A9)
/A10: EDG1.A10, U5.23 (A10)
/A11: EDG1.A11, U5.25 (A11)
/A12: EDG1.A12, U1.17 (I/O), U5.4 (A12)
/A13: EDG1.A13, U1.29 (I/O)
/A15: EDG1.A15, U1.28 (I/O)
/BUSDIR_: EDG1./BUSDIR (~BUSDIR), U1.6 (I/O)
/CS_: J2.6, U1.5 (I/O)
/D0: EDG1.D0, J2.15, U1.16 (I/O), U5.13 (D0)
/D1: EDG1.D1, J2.13, U1.14 (I/O), U5.14 (D1)
/D2: EDG1.D2, J2.11, U1.12 (I/O), U5.15 (D2)
/D3: EDG1.D3, J2.9, U1.11 (I/O), U5.17 (D3)
/D4: EDG1.D4, J2.7, U1.9 (I/O), U5.18 (D4)
/D5: EDG1.D5, J2.5, U1.8 (I/O), U5.19 (D5)
/D6: EDG1.D6, J2.3, U5.20 (D6)
/D7: EDG1.D7, J2.1, U5.21 (D7)
/IORQ_: EDG1./IORQ (~IORQ), U1.4 (I/O)
/MA13: U1.39 (I/O), U5.28 (A13)
/MA14: U1.37 (I/O), U5.29 (A14)
/MA15: U1.36 (I/O), U5.3 (A15)
/MA16: U1.34 (I/O), U5.2 (A16)
/MA17: U1.33 (I/O), U5.30 (A17)
/MA18: U1.31 (I/O), U5.1 (A18)
/RD_: EDG1./RD (~RD), J2.4, U1.43 (GCLK1/IN3), U5.24 (~OE)
/RESET_: EDG1./RESET (~RESET), U1.44 (OE1/IN4)
/SLTSL_: EDG1./SLTSL (~SLTSL), U1.41 (I/O), U5.22 (~CE)
/TCK: J1.1 (TCK), U1.32 (TCK/IO)
/TDI: J1.9 (TDI), U1.7 (TDI/IO)
/TDO: J1.3 (TDO), U1.38 (TDO/IO)
/TMS: J1.5 (TMS), U1.13 (TMS/IO)
/WR_: EDG1./WR (~WR), J2.2, U1.40 (I/O), U5.31 (~PGM)
GND: C1.2, C2.2, C3.2, C4.2, EDG1.GND1 (GND), EDG1.GND2 (GND), J1.2 (GND), J1.10 (GND), J2.14, J2.16, U1.10 (GND), U1.22 (GND), U1.30 (GND), U1.42 (GND), U5.16 (GND)
unnamed: EDG1.SW1, EDG1.SW2
VCC: C1.1, C2.1, C3.1, C4.1, EDG1.+5V1 (+5V), EDG1.+5V2 (+5V), J1.4 (VREF), J2.12, U1.3 (VCC), U1.15 (VCC), U1.23 (VCC), U1.35 (VCC), U5.32 (VCC)

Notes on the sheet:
ATF1502AS-10AU44

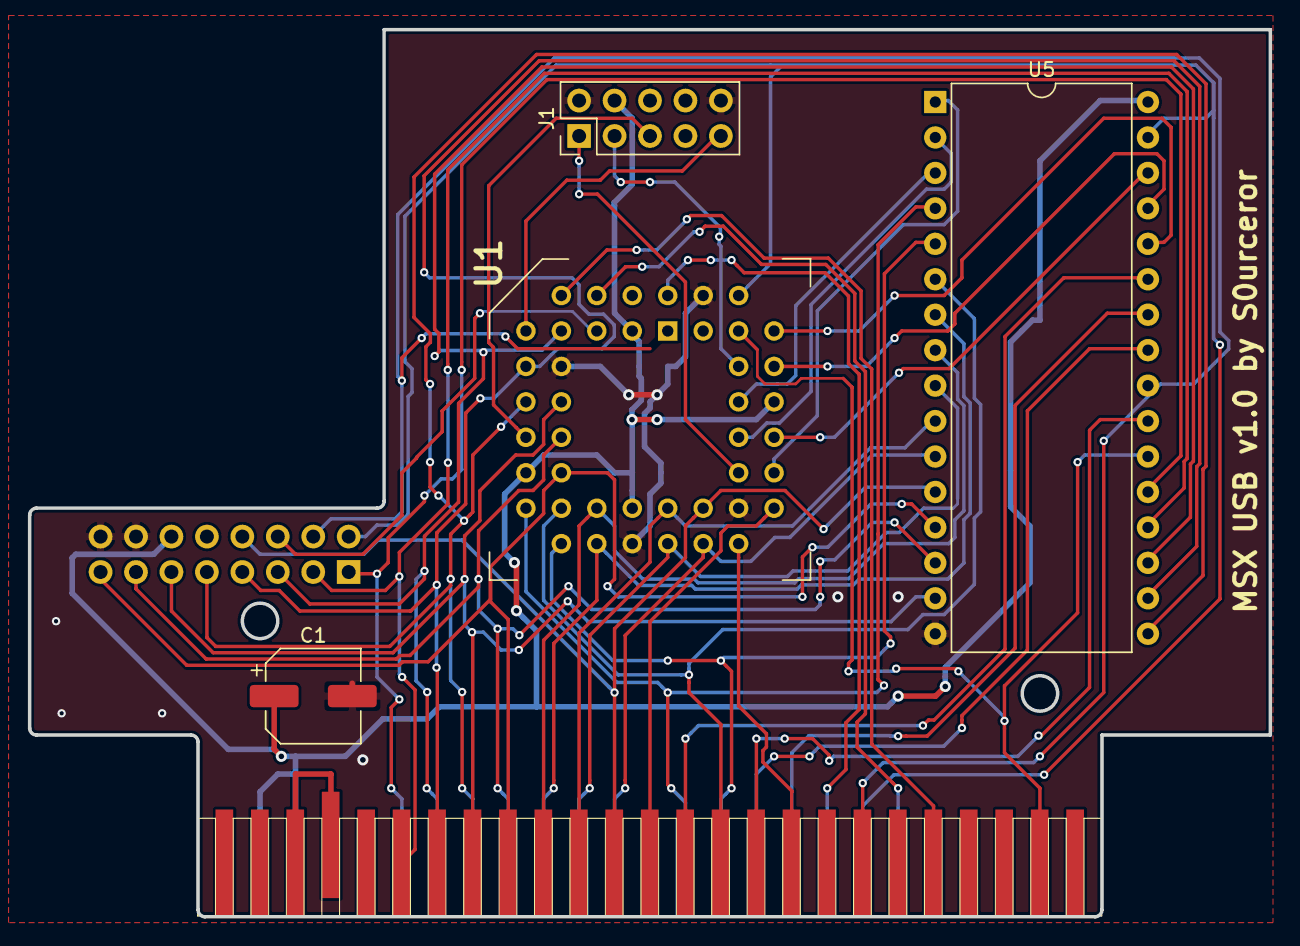
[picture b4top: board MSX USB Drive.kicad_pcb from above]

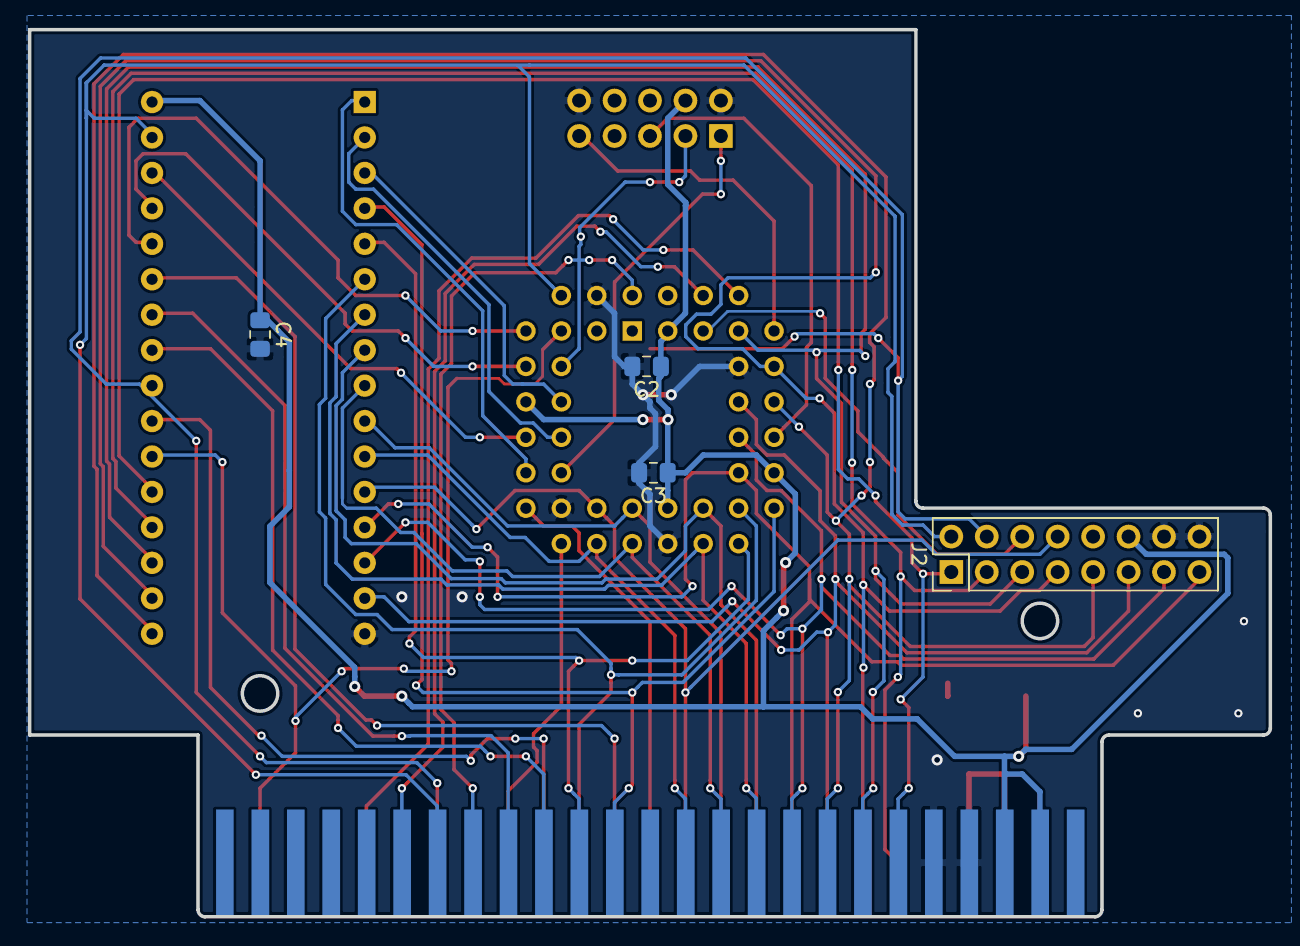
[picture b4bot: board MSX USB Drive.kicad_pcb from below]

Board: 2 copper layers, 88.9 x 63.6 mm, 9 parts (4 on the bottom side), 43 nets.

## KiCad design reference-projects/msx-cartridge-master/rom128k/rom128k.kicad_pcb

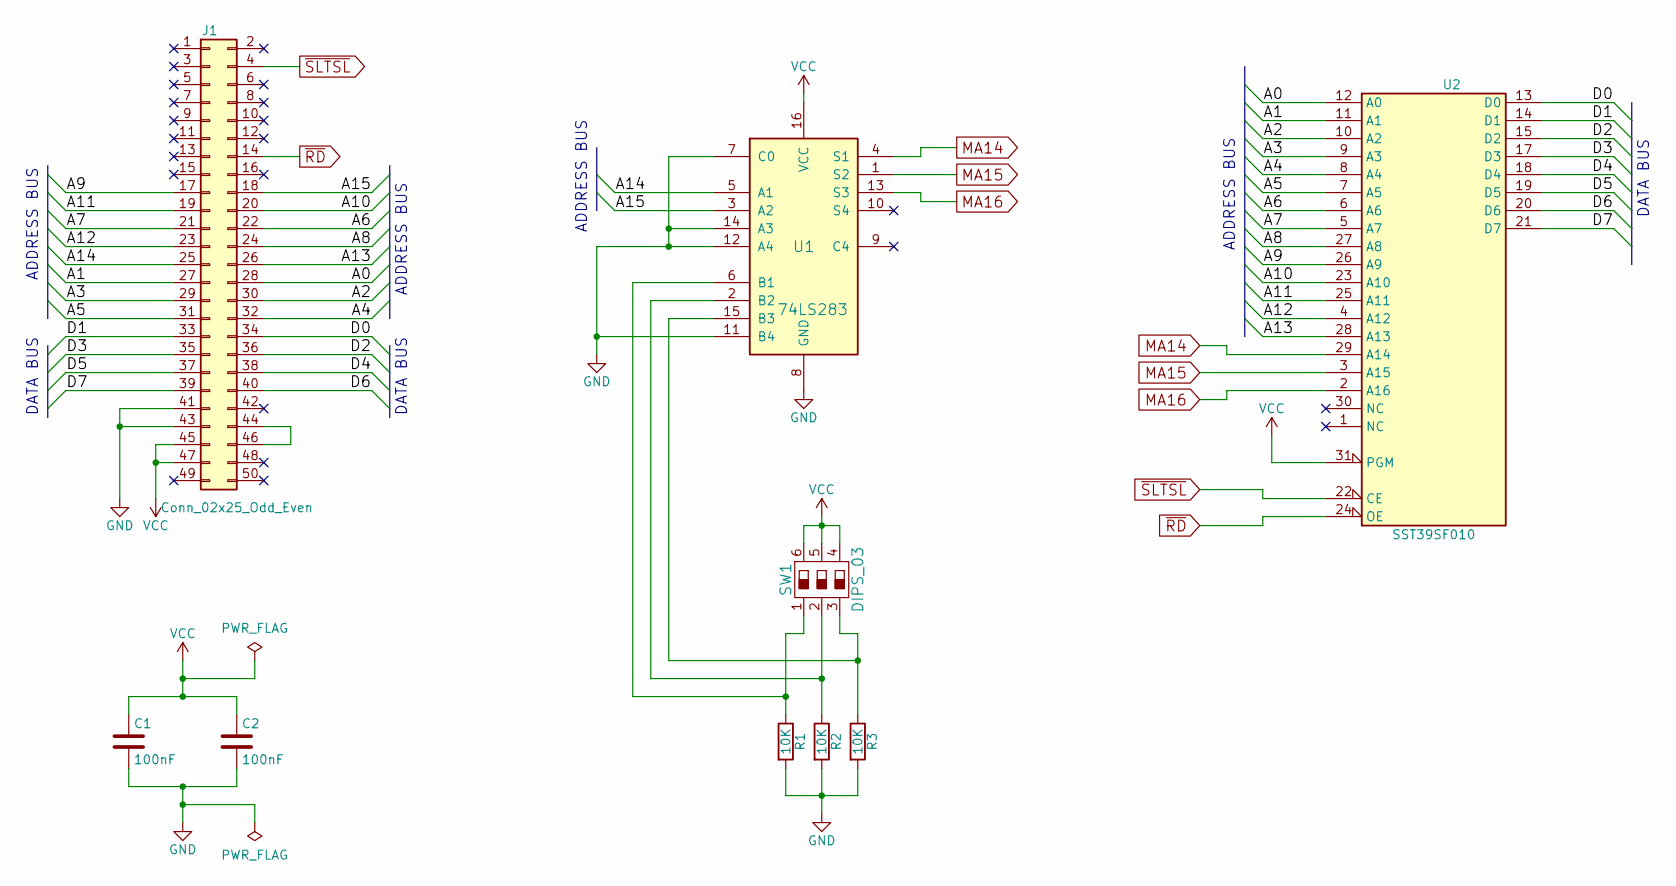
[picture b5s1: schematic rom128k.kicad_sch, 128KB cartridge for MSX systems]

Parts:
C1, C2: 100nF; C_Disc_D6_P5
J1: Conn_02x25_Odd_Even; msx_cartridge
R1, R2, R3: 10K; Resistor_Horizontal_RM10mm
SW1: DIPS_03; DIPS-DS03
U1: 74LS283; DIP-16_W7.62mm
U2: SST39SF010; DIP-32_W15.24mm

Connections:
/A0: J1.28, U2.12 (A0)
/A1: J1.27, U2.11 (A1)
/A2: J1.30, U2.10 (A2)
/A3: J1.29, U2.9 (A3)
/A4: J1.32, U2.8 (A4)
/A5: J1.31, U2.7 (A5)
/A6: J1.22, U2.6 (A6)
/A7: J1.21, U2.5 (A7)
/A8: J1.24, U2.27 (A8)
/A9: J1.17, U2.26 (A9)
/A10: J1.20, U2.23 (A10)
/A11: J1.19, U2.25 (A11)
/A12: J1.23, U2.4 (A12)
/A13: J1.26, U2.28 (A13)
/A14: J1.25, U1.5 (A1)
/A15: J1.18, U1.3 (A2)
/D0: J1.34, U2.13 (D0)
/D1: J1.33, U2.14 (D1)
/D2: J1.36, U2.15 (D2)
/D3: J1.35, U2.17 (D3)
/D4: J1.38, U2.18 (D4)
/D5: J1.37, U2.19 (D5)
/D6: J1.40, U2.20 (D6)
/D7: J1.39, U2.21 (D7)
GND: C1.2, C2.2, J1.41, J1.43, R1.2, R2.2, R3.2, U1.7 (C0), U1.8 (GND), U1.11 (B4), U1.12 (A4), U1.14 (A3), U2.16 (GND)
MA14: U1.4 (S1), U2.29 (A14)
MA15: U1.1 (S2), U2.3 (A15)
MA16: U1.13 (S3), U2.2 (A16)
unnamed: J1.44, J1.46
unnamed: R1.1, SW1.1, U1.6 (B1)
unnamed: R2.1, SW1.2, U1.2 (B2)
unnamed: R3.1, SW1.3, U1.15 (B3)
VCC: C1.1, C2.1, J1.45, J1.47, SW1.4, SW1.5, SW1.6, U1.16 (VCC), U2.31 (PGM), U2.32 (VCC)
~RD: J1.14, U2.24 (OE)
~SLTSL: J1.4, U2.22 (CE)

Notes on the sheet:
ADDRESS BUS
DATA BUS

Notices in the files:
Hardware/Ultra-keyboard/Omega-Keyboard.kicad_pcb:
Copyright (C) 2018, 2020 Sergey Kiselev
reference-projects/msx-cartridge-master/rom128k/rom128k.kicad_pcb:
Copyright (c) 2016 Alvaro Polo
